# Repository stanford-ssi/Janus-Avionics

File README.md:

# Janus-Avionics

Welcome to SSI **Satellite Avionics**! Here, you can find everything you need to navigate our team! This repository covers weekly meeting times, technical trainings, team design documentation, assembly processes, testing procedures, and so much more!

If you have any questions, feel free to contact any AV Co-lead on Slack! Or feel free to email the Kale, the current AV co-lead repo manager at **kalesrz@stanford.edu**.

# Current Leadership (Spring 2026 - Winter 2027)
Satellite Avionics Co-Leads: Clara Zhen, Nimalan Anbhuarasan, Kale Suarez
Satellite Co-Leads: Amy Zheng, River Dowdy, Carson Lauer

Workspace Manager: Clara Zhen
 - Contact For Questions Regarding ES3 and Durand Access

## Weekly Meeting Times
Satellite Avionics has two official meetings each week:

**Weekly Avionics Meeting**
 * **Time:** Thursday, 7:00 PM - 9:00 PM PST
 * **Location:** Check The [#Satellite-Avionics](https://ssi-teams.slack.com/archives/C2L29KW8J) channel in the slack for weekly meeting locations!
 * **Purpose:** Avionics meetings are specifically for AV-specific work, training, and discussions. AV member attendance is expected outside of conflicting Midterms or Finals. Fall quarter attendance is **mandatory** outside of class conflicts or personal health reasons.

**Satsurday Meetings**
 * **Time:** Saturday, 12:00 PM - 2:00 PM PST
 * **Location:** Check The [#Satellite-Avionics](https://ssi-teams.slack.com/archives/C2L29KW8J) channel in the slack for weekly meeting locations!
 * **Purpose**: Satsurday meetings are Satellite Avionics Full-Team work days! Every subteam will be meeting at this time. This can sometimes happen collectively and sometimes separately. Fall quarter will mostly be dedicated to AV specific onboarding training and early satellite development. Fall quarter attendance is **mandatory** outside of class conflicts or personal health reasons.

## Getting On Slack!
In order to join our weekly meetings, you'll need to join our slack to figure out where were meeting! You can join our slack by clicking [here](https://ssi-teams.slack.com/signup). Once you're on the slack, go ahead and add the [#satellite-avionics](https://ssi-teams.slack.com/archives/C2L29KW8J) channel. You should also make sure to join all of these important channels!
* [#satellite-avionics](https://ssi-teams.slack.com/archives/C2L29KW8J)
    - All AV communication and announcements happen here! You need to be in this channel to know
      where were meeting for the week.
* [#satellites](https://ssi-teams.slack.com/archives/C04JL94F9)
    - General Satellites team communications and announcements happen here!
* [#satellite-systems](https://ssi-teams.slack.com/archives/C4UL92684)
    - System-wide meeting plans and discussions with other subteams on Satellites happen here!
* [#esiii](https://ssi-teams.slack.com/archives/C3YLQTN87)
    - Our Lab Space!!!
* [#doorbell](https://ssi-teams.slack.com/archives/CE360LHD0)
    - If you don't have keycard access to End Station III (ES3), run the `\doorbell` command to get someone to come open the door if anyones in ES3.

## Accessing Our Workspaces!
We primarily operate out of two buildings, End Station III (Deep Lab / Hepl South), and the Durand Aeronautics & Astronautics building. End Station III is a little difficult to find the first time, so please ask leads in the slack if you get lost!

### End Station III (Deep Lab / Hepl South)
**Address:** 491 S Service Rd, Stanford, CA 94305\
**Google Maps Link:** [Stanford Student Space Initiative](https://maps.app.goo.gl/ZUDnvgVmYYjSPFpS8)\
**Access Entrance:** Please enter through the **North Entrance** on Service Road (As Seen Below). After-Hours/Weekend Access requires that you obtain keycard access.

### Stanford University Aeronautics & Astronautics (Durand)
**Address:** 496 Lomita Mall, Stanford, CA 94305\
**Google Maps Link:** [Stanford University Aeronautics & Astronautics (Durand)](https://maps.app.goo.gl/TxbG7z5m1ypoC3tW7)\
**Access Entrance:** Any entrance can be used given you have obtained Durand keycard access. Otherwise, feel free to message a lead in the [#satellite-avionics](https://ssi-teams.slack.com/archives/C2L29KW8J) slack channel if you need help getting in!

### Gaining Access
To be able to gain keycard access to these workspaces and to be able to enter without another member to scan you in, you must complete the ES3 Lab safety trainings and complete all the steps listed on the [ES3 Access Guide](https://sites.google.com/stanford.edu/ssi/end-station-iii/keycard-access-for-es3). You will need to use your Stanford Email in order to view the guide.

## Additional Helpful Links / Quick Access
[Stanford SSI Wiki: Satellites](https://ssi-wiki.stanford.edu/Category:Satellites)
 - SSI's official wiki page (notice: sometimes outdated, but there is some pretty useful information about the team and important definitions if you'd like to check it out.)

[SSI Slack Signup](https://ssi-teams.slack.com/signup)

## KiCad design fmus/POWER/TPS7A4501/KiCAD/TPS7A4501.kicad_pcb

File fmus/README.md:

# Functional Modular Units

## A quick note on FMUs
A Functional Modular Unit (FMU) is SATS AV’s internal name for the following concept: An Integrated Circuit, Filter, Converter, or any other group of external components that fulfill a single task or purpose that can be accessibly integrated into any system that follows a set communication standard. FMUs must be easily integrable into boards that meet certain system-level defined power and communication standards and that require the functionality the particular FMU provides.

In essense, FMUs are the building blocks for our satellites, and using them simplifies our development process by 10 fold as any new designed will not have to worry about integrating a chip everytime they want to use it in a new design; they can simply skim a description of the FMU, run some calculations to shift values, and move on with their day.

### FMU structure

```bash
[Subsystem]
|   [FMU]
|    | - **FMU Name - Datasheet.pdf**
|    | - **FMU Name - Module/**
|    |   | - KiCad Project Files
|    | - **FMU Name - Notes.md** # Notes special considerations that should be looked at when designing using this component. Often just ripped straight from the datasheet, but would be easy to miss if not brought to our attention.
|    | - **FMU_Name_Calculator.py** # Python script with functions implementing design calculations from datasheet for easy recompute.
```

As an example, please look at the following structure of the TPS7A4501 Variable output switching converter IC:

Here, you can see the aforemention structure. The TPS7A4501 is a power subystem IC. A file for its datasheet, application notes, and a python calculator to determine component values are all within the document. **ALL FMUs** must follow this structure to ensure reliability of use and knowledge transfer moving forward. 

Abstraction is the practice of hiding low level details of an implementation of a system in order to only demonstrate a component's large-scale purpose and function in a system. The primary goal of FMU’s are to completely abstract away configurable external components that change the way the FMU behaves. For example, if a buck converter determines its output voltage or stability by additional capacitors or resistors, these should not be visible outside a hierarchical abstraction or module KiCad. 

An FMU’s functional properties should be noted as a comment next to the FMU, rather than what external components it implemented.

Using the TPS7A4501 as an example:

This is a single TPS7A4501 FMU with a full schematic. As you can see, every component is exposed with its value visible. However, this is one layer down in the hierarchical tree.

If we go up to the root schematics, we see the following:

As seen, all components that do not directly interact with external modules are hidden. We use hierarchical labels to abstract function.

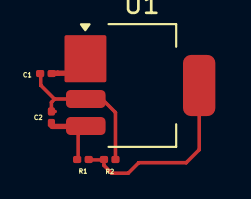
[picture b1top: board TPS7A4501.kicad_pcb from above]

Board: 2 copper layers, 5 parts (0 on the bottom side), 4 nets.

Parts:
C1, C2: 10 uF; C_0201_0603Metric
R1: 4.22k; R_0201_0603Metric
R2: 4k; R_0201_0603Metric
U1: TPS7A4501; SOT-223-5

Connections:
/TPS7A4501/VIN: C1.1, U1.1 (~SHDN), U1.2 (IN)
/TPS7A4501/VOUT: C2.1, R1.1, U1.4 (OUT)
GND: C1.2, C2.2, R2.2, U1.3 (GND)
unnamed: R1.2, R2.1, U1.5 (ADJ)

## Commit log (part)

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2026-06-04 test document
2026-06-04 test
2026-06-04 removed test files
